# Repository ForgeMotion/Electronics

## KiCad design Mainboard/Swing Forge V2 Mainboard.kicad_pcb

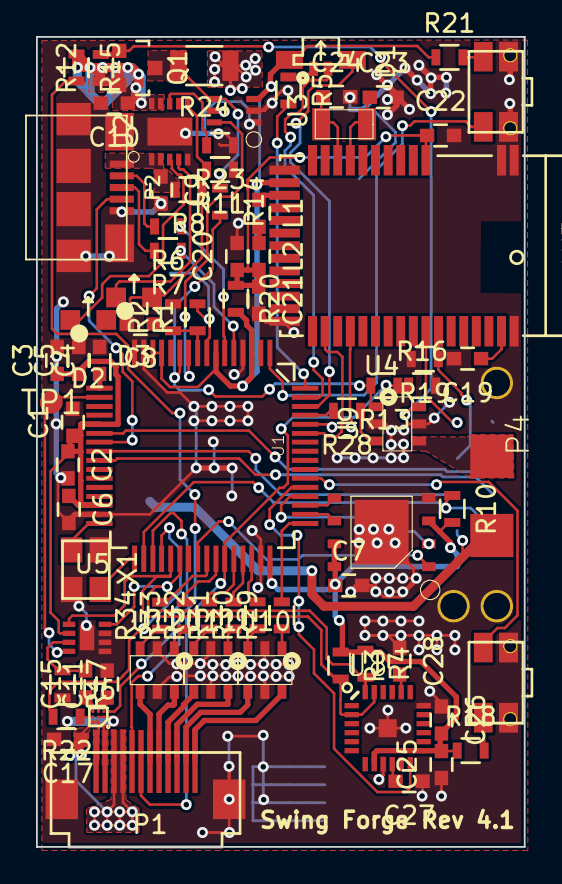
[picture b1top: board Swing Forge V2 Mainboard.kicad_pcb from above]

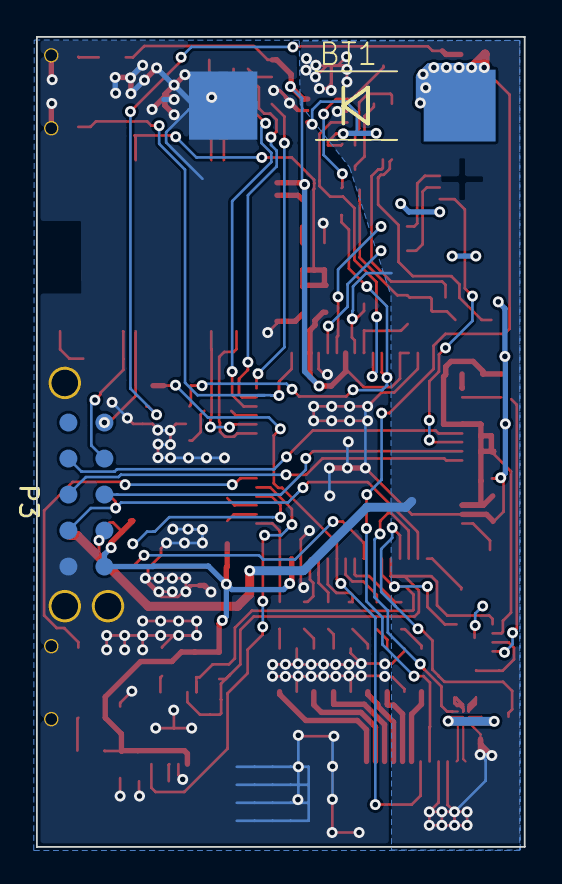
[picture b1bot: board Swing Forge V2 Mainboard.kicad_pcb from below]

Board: 2 copper layers, 27.1 x 45.0 mm, 81 parts (2 on the bottom side), 84 nets.

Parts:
BT1: Lipo 1S 1Ah; SMB-DIODE
C1, C9, C20, C25: 1uF; C_0603
C2, C3, C4, C5, C6, C7, C8, C22, C26, C27: 0.1uF; C_0603
C10, C17: 10uF; C_0603
C11, C15: 0.47uF; C_0603
C19: 47nF; C_0603
C21: 100pF; C_0603
C23, C24: 12pF; C_0603
C28: 2.2nF; C_0603
D1: LED_RGBA; LTST-S310
D2: RED; LTST-S270
D3: GREEN; LTST-S270
L1: 10uH; C_0603
L2: 15nH; C_0603
P1: FPC Connector; FPC_Socket_12pin
P2: USB_micro_B; MICRO-B_USB
P3: CommonLink-ProgPads; commonLink-pads
P4: MOT_CHEST; SMB-DIODE
Q1: DMG3415U; SOT-23
R1, R16: 43k*; R_0603
R2: 10k*; R_0603
R3, R4, R10: 3k3; R_0603
R5, R8, R28, R29, R30, R31, R32, R33, R34: 150R; R_0603
R6, R7: 33R; R_0603
R11: 1k0*; R_0603
R12, R17: 100k; R_0603
R13: 270k*; R_0603
R14, R15, R18, R19, R21, R23: 10k; R_0603
R20: 0R; R_0603
R22: 0-100k; R_0603
R24: 0R010; R_1206
SW1, SW2: Side Tactile Sw; PTS840_PK_alt_2pin
TP1: TP_1; PAD.03X.05
U1: MK20DX256VLH7; QFP50P1200X1200X160-64N
U2: MCP73833-FCI/MF; DFN-10-1EP_3x3mm_Pitch0.5mm
U3: INA199x2DCK; SC70
U4: W25Q64FVZP; WSON-8-6x5
U5: MAX5395LATA; MAX5395
U6: MAX98304; MAX38309
U7: MDBT40
U8: MPU-6050; MPU-6050_QFN-24
U9, U10, U11, U12: DMN2215UDM; SOT-26
X1: 16 MHz; crystal_FA238-TSX3225
X2: 32.768kHz; ABS07AIG

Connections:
+3V3: C1.1, C2.1, C3.1, C5.1, C6.1, C7.1, C25.2, C26.2, D1.4, P3.10, R3.1, R4.1, R10.2, R18.1, R20.2, R21.1, U1.3, U1.7, U1.13, U1.14, U1.21, U1.30, U1.48, U3.3, U4.3, U4.7, U4.8, U5.6, U7.14, U8.8, U8.13
+BATT: C17.1, P1.9, P1.10, P3.8, P4.1, R1.2, R24.1, U1.8, U3.5, U6.A3
/BATT_SENSE: C8.1, R1.1, R2.1, U1.9
/BLE/BLE_RX: U1.60, U7.29
/BLE/BLE_SWDCLK: P3.4, R19.1, U7.36
/BLE/BLE_SWDIO: P3.2, U7.35
/BLE/BLE_TX: U1.59, U7.27
/BLE/DCC: L1.1, U7.15
/DAC_audio_system/AUDIO_GAIN: R22.2, U1.36
/DAC_audio_system/AUDIO_SHUTDOWN: U1.35, U6.C1
/DAC_audio_system/DAC_SIGNAL: TP1.1, U1.18, U5.8
/DAC_audio_system/FLASH_CS: U1.40, U4.1
/DAC_audio_system/Speaker_OUT+: P1.12, U6.A2
/DAC_audio_system/Speaker_OUT-: P1.11, U6.A1
/LED_B: D1.3, U1.62
/LED_G: D1.2, U1.63
/LED_R: R5.2, U1.64
/Lipo_System/CHG+: BT1.1, C10.1, Q1.2, R12.1, R15.1, U2.9, U2.10
/Lipo_System/I_SENSE: U1.10, U3.6
/Lipo_System/SHUNT+: Q1.3, R14.1, R24.2, U3.4
/Lipo_System/USB+: C9.1, P2.1, R8.2, U2.1, U2.2
/Lipo_System/USB_D+: R7.1, U1.5
/Lipo_System/USB_D-: R6.1, U1.6
/Lipo_System/USB_ID: P2.4, U1.23
/MotionBoard/IMU_INT: U1.53, U8.12
/MotorDrivers/MOT_IN_1: R28.2, U1.61
/MotorDrivers/MOT_IN_2: R29.2, U1.49
/MotorDrivers/MOT_IN_3: R30.2, U1.46
/MotorDrivers/MOT_IN_4: R31.2, U1.45
/MotorDrivers/MOT_IN_5: R32.2, U1.44
/MotorDrivers/MOT_IN_6: R33.2, U1.42
/MotorDrivers/MOT_IN_7: R34.2, U1.41
/MotorDrivers/MOT_OUT_1: P4.2, U9.4
/MotorDrivers/MOT_OUT_2: P1.1, U10.6
/MotorDrivers/MOT_OUT_3: P1.2, U10.4
/MotorDrivers/MOT_OUT_4: P1.3, U11.6
/MotorDrivers/MOT_OUT_5: P1.4, U11.4
/MotorDrivers/MOT_OUT_6: P1.5, U12.6
/MotorDrivers/MOT_OUT_7: P1.6, U12.4
/RST: P3.7, R10.1, U1.34
/SWDCLK: P3.3, U1.22
/SWDIO: P3.5, U1.25
/SWO: P3.6, U1.24
/VOL_DOWN: R18.2, SW2.1, U1.54
/VOL_UP: R21.2, SW1.1, U1.1
GND: BT1.2, C1.2, C2.2, C3.2, C4.2, C5.2, C6.2, C7.2, C8.2, C9.2, C10.2, C11.2, C17.2, C19.2, C20.2, C21.2, C22.2, C23.2, C24.2, C25.1, C26.1, C27.1, C28.1, P1.~, P2.5, P2.6, P3.9, P3.11, P3.12, P3.13, R2.2, R11.1, R16.2, R17.2, R19.2, R23.1, SW1.2, SW2.2, U1.4, U1.15, U1.16, U1.31, U1.47, U2.5, U2.EP, U3.1, U3.2, U4.4, U4.9, U5.1, U5.2, U5.3, U5.9, U6.B1, U6.B2, U7.1, U7.2, U7.13, U7.25, U7.42, U8.9, U8.18, U9.2, U9.5, U10.2, U10.5, U11.2, U11.5, U12.2, U12.5, X1.3
MISO: U1.52, U4.2
MOSI: U1.51, U4.5
unnamed: C4.1, U1.17
unnamed: C11.1, U6.C2
unnamed: C15.1, U6.C3
unnamed: C15.2, R17.1, U5.7
unnamed: C19.1, U7.41
unnamed: C20.1, C21.1, C22.1, L2.2, R20.1, U7.3
unnamed: C23.1, U7.9, X2.1
unnamed: C24.1, U7.10, X2.2
unnamed: C27.2, U8.10
unnamed: C28.2, U8.20
unnamed: D1.1, R5.1
unnamed: D2.1, U2.3
unnamed: D2.2, D3.2, R8.1
unnamed: D3.1, U2.4
unnamed: L1.2, L2.1
unnamed: P2.2, R6.2
unnamed: P2.3, R7.2
unnamed: R11.2, U2.6
unnamed: R22.1, U6.B3
unnamed: R23.2, U2.8
unnamed: R28.1, U9.3
unnamed: R29.1, U10.1
unnamed: R30.1, U10.3
unnamed: R31.1, U11.1
unnamed: R32.1, U11.3
unnamed: R33.1, U12.1
unnamed: R34.1, U12.3
unnamed: U1.32, X1.1
unnamed: U1.33, X1.2
PWR_NFET_D: Q1.1, R12.2, U9.6
PWR_NFET_G: R13.2, R14.2, U1.11, U9.1
PWR_SW+: P1.8, R15.2
PWR_SW-: P1.7, R13.1, R16.1, U1.43
SCK: U1.50, U4.6
SCL: R3.2, U1.37, U5.5, U8.2, U8.23
SDA: R4.2, U1.38, U5.4, U8.24

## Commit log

2018-01-03 Initial commit of 10.0
2018-01-16 Distroboard - schematic finished, PCB in progress
